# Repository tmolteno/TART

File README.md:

# Transient Array Radio Telescope

This repository has been ARCHIVED. It has been split into many smaller repositories under the tart-telescope organization.
see (https://github.com/tart-telescope) for details

The [Transient Array Radio Telescope](https://en.wikipedia.org/wiki/Transient_Array_Radio_Telescope) (TART) is a low-cost 24-element aperture synthesis array
developed by the [Elec Research Group](http://elec.ac.nz) at the University of Otago

 ![All-sky image from a TART telescope][tart_image] 

The TART software and hardware designs are released as open-source designs and are
licensed under the GPL v3.

The authors of the first version of the TART are Tim Molteno, Charles Shaw, Max 
Scheel and Phil Brown. Enquries about the TART should be addressed to Tim Molteno (tim@elec.ac.nz). 

[Connect to our development radio telescope here](https://tart.elec.ac.nz "Online Telescopes")

## Hardware

The TART hardware is designed using a combination of KiCAD (newest boards) and
CadSoft's Eagle package. These designs are located in the [hardware](hardware/README.md) folder. 

## Firmware

The TART uses an FPGA to synchronize data from each receiver. The code for this in the 
Verilog language is in the [hardware/FPGA](hardware/FPGA/README.md) directory

## Installation

See the  [Installation Instructions](INSTALL.md) file for more detail on installation.

[tart_image]: https://github.com/tmolteno/TART/blob/master/doc/img/tart_image.jpg "TART All-Sky Image"

## Telescope API documentation

The [Telescope API documentation](https://tart.elec.ac.nz/doc/) describes how the TART is controlled via the network for configration and data retrieval.

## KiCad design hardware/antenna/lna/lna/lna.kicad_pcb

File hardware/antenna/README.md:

# Antenna Design for TART

## Conventional GPS antenna

The TART telescope can operate with standard off-the-shelf antennas

 ![All-sky antenna on a pedestal (for snow clearance)][antenna_image] 

## Other Antenna Ideas

Goal. A simple radiation pattern insensitive to polarization with approximately 90 degree beam width.

[antenna_image]: https://github.com/tmolteno/TART/blob/master/doc/img/antenna.jpg "All-sky GPS antenna"

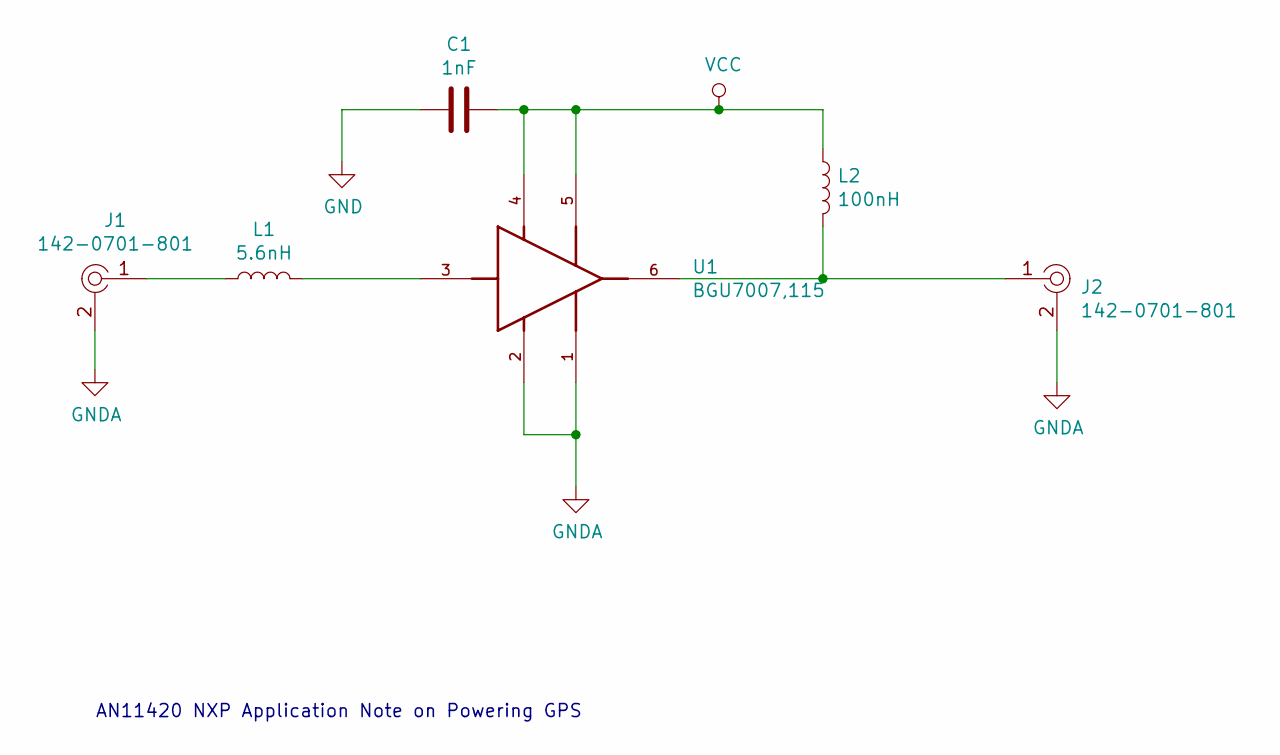
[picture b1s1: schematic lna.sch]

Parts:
C1: 1nF; C_0402_1005Metric
J1, J2: 142-0701-801; SMA_Amphenol_132289_EdgeMount; MPN 142-0701-801; Digi-Key_PN J502-ND
L1: 5.6nH; L_0402_1005Metric
L2: 100nH; L_0402_1005Metric
U1: BGU7007,115; PSON50P100X145X50-6N

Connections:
GND: C1.1
GNDA: J1.2, J2.2, U1.1 (GND1), U1.2 (GND2)
unnamed: J1.1, L1.1
unnamed: J2.1, L2.2, U1.6 (RF_OUT)
unnamed: L1.2, U1.3 (RF_IN)
VCC: C1.2, L2.1, U1.4 (VCC), U1.5 (ENABLE)

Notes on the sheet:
AN11420 NXP Application Note on Powering GPS

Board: 2 copper layers, 6 parts (0 on the bottom side), 5 nets, no tracks yet.

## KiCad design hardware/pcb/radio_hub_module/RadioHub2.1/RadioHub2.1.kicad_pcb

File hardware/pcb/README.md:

At the moment TART consists of three different PCBs:

1. (24x) Radio module (RF front end)
2. (4x) Radio hub module (jitter cleaner, power supply, 485 transceiver and base for 6 Radio modules)
3. (1x) Base station module (485 transceiver, oscillator, power supply, host for acquisition FPGA and Raspberry Pi)

base_station, radio_hub_module and radio_module are the original designs used for all currently built up TART's (as of Feb 2019). The base_station folder is a KIcad project, while radio_hub_module and radio_module are created in Eagle PCB.

The *201902 folder are the above converted and updated to KIcad 5 projects.

BOM html and CSV files are included. These are generated by the github.com:SchrodingersGat/KiBoM.git plugin.

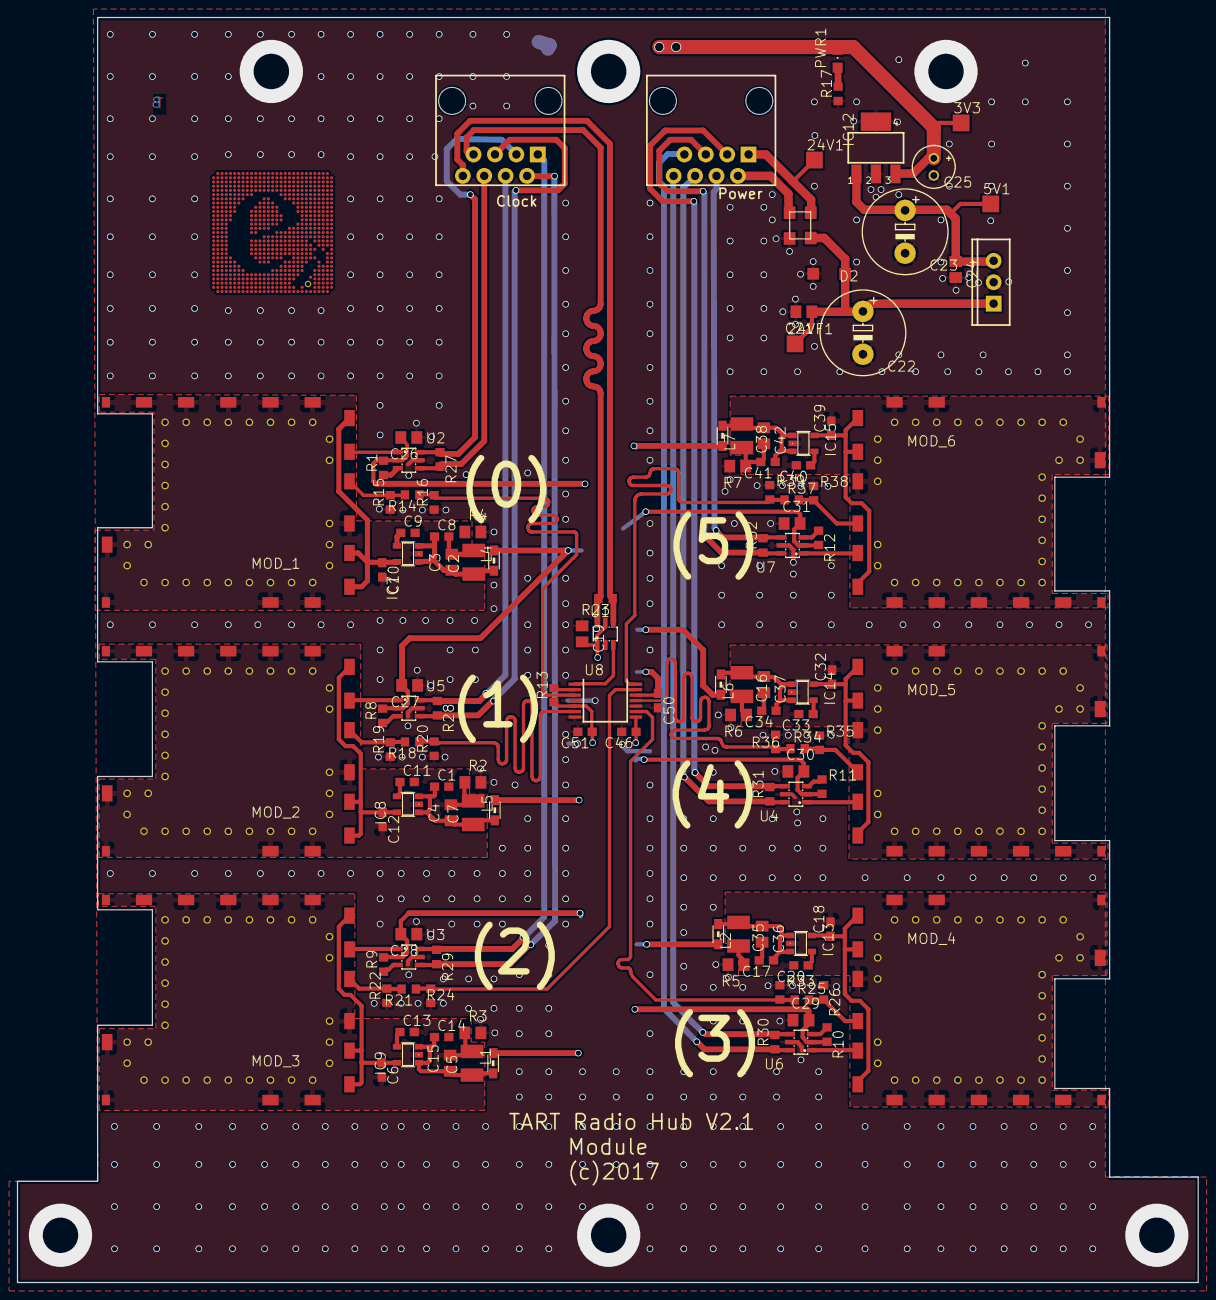
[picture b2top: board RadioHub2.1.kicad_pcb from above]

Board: 2 copper layers, 140.0 x 150.0 mm, 122 parts (0 on the bottom side), 71 nets.

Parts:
3V3, 5V1, 24V1, 24VF1: TPSQTP20SQ; TP20SQ
C1, C6, C8, C10, C12, C14, C17, C18, C32, C34, C39, C41: 1u; C0603
C2, C5, C7, C16, C35, C38: 220u; C1210
C3, C4, C15, C36, C37, C42: 0.1; C0805
C9, C11, C13, C20, C33, C40: 10n; C0603
C19, C21, C24, C26, C27, C28, C29, C30, C31: 0.1u; C0805
C22, C23: 100u; E5-10,5
C25: 10uF; E2-5
C46, C50, C51: 0.1; C0603
CON3, CON4: RJ45-8PTH; RJ45-8
D2: SMF24A; SOD123
IC7, IC8, IC9, IC13, IC14, IC15: TPS78227DDCR; SOT23-5
IC11: OKI78s05; TO220-IGO
IC12: SPX3940; SOT223
L1, L2, L4, L5, L6, L7: WE-CBF_0805; 0805
L3: ACM3225-601-2P-T001
MOD_1, MOD_2, MOD_3, MOD_4, MOD_5, MOD_6: GPS_RADIO_MODULE
PWR1: Red; CHIPLED_0805
R1, R8, R9, R10, R11, R12, R13, R17: 1k; R0603
R2, R3, R4, R5, R6, R7: 0 Ohm; R0805
R14, R18, R21, R25, R34, R37: 37.3; R0603
R15, R16, R19, R20, R22, R24, R26, R33, R35, R36, R38, R39: 151; R0603
R23, R27, R28, R29, R30, R31, R32: 100; R0603
U1: MAX3284E; SOT23-6L
U2, U3, U4, U5, U6, U7: MAX3295AUT; SOT23-6L
U8: CDCLVC1106; SSOP14
U$1: LOGO15X15; LOGO

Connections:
+3V3: 3V3.TP, C19.2, C25.+, C26.2, C27.2, C28.2, C29.2, C30.2, C31.2, C46.1, C50.1, C51.1, IC12.3, L1.1, L2.1, L4.1, L5.1, L6.1, L7.1, PWR1.C, R1.2, R8.2, R9.2, R10.2, R11.2, R12.2, R13.1, U1.1, U1.5, U2.2, U3.2, U4.2, U5.2, U6.2, U7.2, U8.5, U8.8, U8.12
+5V: 5V1.TP, C23.+, C24.1, IC11.OUT, IC12.1
/RadioHub2.1_2/+24V_CABLE: 24V1.TP, CON4.1, L3.1
/RadioHub2.1_2/CLK_N: CON3.7, R23.2, U1.6
/RadioHub2.1_2/CLK_P: CON3.8, R23.1, U1.4
/RadioHub2.1_2/GND_CABLE: CON4.2, L3.2
/RadioHub2.1_4/CLK0Y: R14.1, R16.2, U8.3
/RadioHub2.1_4/CLK1Y: R18.1, R20.2, U8.6
/RadioHub2.1_4/CLK2Y: R21.1, R24.2, U8.13
/RadioHub2.1_4/CLK3Y: R25.1, R33.2, U8.9
/RadioHub2.1_4/CLK4Y: R34.1, R36.2, U8.11
/RadioHub2.1_4/CLK5Y: R37.1, R39.2, U8.14
CLK0: MOD_1.CKIN@13, R14.2, R15.2
CLK1: MOD_2.CKIN@13, R18.2, R19.2
CLK2: MOD_3.CKIN@13, R21.2, R22.2
CLK3: MOD_4.CKIN@13, R25.2, R26.2
CLK4: MOD_5.CKIN@13, R34.2, R35.2
CLK5: MOD_6.CKIN@13, R37.2, R38.2
DT0_N: CON3.6, R27.2, U2.4
DT0_P: CON3.3, R27.1, U2.6
DT1_N: CON3.5, R28.2, U5.4
DT1_P: CON3.4, R28.1, U5.6
DT2_N: CON3.2, R29.2, U3.4
DT2_P: CON3.1, R29.1, U3.6
DT3_N: CON4.8, R30.2, U6.4
DT3_P: CON4.7, R30.1, U6.6
DT4_N: CON4.3, R31.2, U4.4
DT4_P: CON4.6, R31.1, U4.6
DT5_N: CON4.4, R32.2, U7.4
DT5_P: CON4.5, R32.1, U7.6
DT_0: MOD_1.DT@12, U2.1
DT_1: MOD_2.DT@12, U5.1
DT_2: MOD_3.DT@12, U3.1
DT_3: MOD_4.DT@12, U6.1
DT_4: MOD_5.DT@12, U4.1
DT_5: MOD_6.DT@12, U7.1
GND: C19.1, C21.2, C22.-, C23.-, C24.2, C25.-, C26.1, C27.1, C28.1, C29.1, C30.1, C31.1, C46.2, C50.2, C51.2, D2.A, IC11.GND, IC12.2, IC12.4, L3.3, R2.2, R3.2, R4.2, R5.2, R6.2, R7.2, R15.1, R16.1, R17.1, R19.1, R20.1, R22.1, R24.1, R26.1, R33.1, R35.1, R36.1, R38.1, R39.1, U1.2, U2.5, U3.5, U4.5, U5.5, U6.5, U7.5, U8.4, U8.7, U8.10
unnamed: 24VF1.TP, C21.1, C22.+, D2.C, IC11.IN, L3.4
unnamed: C1.1, C4.1, C7.1, IC8.1, IC8.3, L5.2
unnamed: C1.2, C4.2, C7.2, C11.2, C12.2, IC8.2, MOD_2.GND@1, MOD_2.GND@2, MOD_2.GND@3, MOD_2.GND@4, MOD_2.GND@5, MOD_2.GND@6, MOD_2.GND@7, MOD_2.GND@8, MOD_2.GND@9, MOD_2.GND@10, MOD_2.GND@14, MOD_2.V1, MOD_2.V2, MOD_2.V3, MOD_2.V4, MOD_2.V5, MOD_2.V6, MOD_2.V7, MOD_2.V8, MOD_2.V9, MOD_2.V10, MOD_2.V11, MOD_2.V12, MOD_2.V13, MOD_2.V14, MOD_2.V15, MOD_2.V16, MOD_2.V17, MOD_2.V18, MOD_2.V19, MOD_2.V20, MOD_2.V21, MOD_2.V22, MOD_2.V23, MOD_2.V24, MOD_2.V25, MOD_2.V26, MOD_2.V27, MOD_2.V28, MOD_2.V29, MOD_2.V30, R2.1
unnamed: C2.1, C3.1, C8.1, IC7.1, IC7.3, L4.2
unnamed: C6.1, IC9.5, MOD_3.2V8@11, MOD_3.2V8@15, MOD_3.2V8@16
unnamed: C9.1, IC7.4
unnamed: C10.1, IC7.5, MOD_1.2V8@11, MOD_1.2V8@15, MOD_1.2V8@16
unnamed: C2.2, C3.2, C8.2, C9.2, C10.2, IC7.2, MOD_1.GND@1, MOD_1.GND@2, MOD_1.GND@3, MOD_1.GND@4, MOD_1.GND@5, MOD_1.GND@6, MOD_1.GND@7, MOD_1.GND@8, MOD_1.GND@9, MOD_1.GND@10, MOD_1.GND@14, MOD_1.V1, MOD_1.V2, MOD_1.V3, MOD_1.V4, MOD_1.V5, MOD_1.V6, MOD_1.V7, MOD_1.V8, MOD_1.V9, MOD_1.V10, MOD_1.V11, MOD_1.V12, MOD_1.V13, MOD_1.V14, MOD_1.V15, MOD_1.V16, MOD_1.V17, MOD_1.V18, MOD_1.V19, MOD_1.V20, MOD_1.V21, MOD_1.V22, MOD_1.V23, MOD_1.V24, MOD_1.V25, MOD_1.V26, MOD_1.V27, MOD_1.V28, MOD_1.V29, MOD_1.V30, R4.1
unnamed: C11.1, IC8.4
unnamed: C12.1, IC8.5, MOD_2.2V8@11, MOD_2.2V8@15, MOD_2.2V8@16
unnamed: C13.1, IC9.4
unnamed: C5.2, C6.2, C13.2, C14.2, C15.2, IC9.2, MOD_3.GND@1, MOD_3.GND@2, MOD_3.GND@3, MOD_3.GND@4, MOD_3.GND@5, MOD_3.GND@6, MOD_3.GND@7, MOD_3.GND@8, MOD_3.GND@9, MOD_3.GND@10, MOD_3.GND@14, MOD_3.V1, MOD_3.V2, MOD_3.V3, MOD_3.V4, MOD_3.V5, MOD_3.V6, MOD_3.V7, MOD_3.V8, MOD_3.V9, MOD_3.V10, MOD_3.V11, MOD_3.V12, MOD_3.V13, MOD_3.V14, MOD_3.V15, MOD_3.V16, MOD_3.V17, MOD_3.V18, MOD_3.V19, MOD_3.V20, MOD_3.V21, MOD_3.V22, MOD_3.V23, MOD_3.V24, MOD_3.V25, MOD_3.V26, MOD_3.V27, MOD_3.V28, MOD_3.V29, MOD_3.V30, R3.1
unnamed: C5.1, C14.1, C15.1, IC9.1, IC9.3, L1.2
unnamed: C16.1, C34.1, C37.1, IC14.1, IC14.3, L6.2
unnamed: C16.2, C32.2, C33.2, C34.2, C37.2, IC14.2, MOD_5.GND@1, MOD_5.GND@2, MOD_5.GND@3, MOD_5.GND@4, MOD_5.GND@5, MOD_5.GND@6, MOD_5.GND@7, MOD_5.GND@8, MOD_5.GND@9, MOD_5.GND@10, MOD_5.GND@14, MOD_5.V1, MOD_5.V2, MOD_5.V3, MOD_5.V4, MOD_5.V5, MOD_5.V6, MOD_5.V7, MOD_5.V8, MOD_5.V9, MOD_5.V10, MOD_5.V11, MOD_5.V12, MOD_5.V13, MOD_5.V14, MOD_5.V15, MOD_5.V16, MOD_5.V17, MOD_5.V18, MOD_5.V19, MOD_5.V20, MOD_5.V21, MOD_5.V22, MOD_5.V23, MOD_5.V24, MOD_5.V25, MOD_5.V26, MOD_5.V27, MOD_5.V28, MOD_5.V29, MOD_5.V30, R6.1
unnamed: C17.1, C35.1, C36.1, IC13.1, IC13.3, L2.2
unnamed: C17.2, C18.2, C20.2, C35.2, C36.2, IC13.2, MOD_4.GND@1, MOD_4.GND@2, MOD_4.GND@3, MOD_4.GND@4, MOD_4.GND@5, MOD_4.GND@6, MOD_4.GND@7, MOD_4.GND@8, MOD_4.GND@9, MOD_4.GND@10, MOD_4.GND@14, MOD_4.V1, MOD_4.V2, MOD_4.V3, MOD_4.V4, MOD_4.V5, MOD_4.V6, MOD_4.V7, MOD_4.V8, MOD_4.V9, MOD_4.V10, MOD_4.V11, MOD_4.V12, MOD_4.V13, MOD_4.V14, MOD_4.V15, MOD_4.V16, MOD_4.V17, MOD_4.V18, MOD_4.V19, MOD_4.V20, MOD_4.V21, MOD_4.V22, MOD_4.V23, MOD_4.V24, MOD_4.V25, MOD_4.V26, MOD_4.V27, MOD_4.V28, MOD_4.V29, MOD_4.V30, R5.1
unnamed: C18.1, IC13.5, MOD_4.2V8@11, MOD_4.2V8@15, MOD_4.2V8@16
unnamed: C20.1, IC13.4
unnamed: C32.1, IC14.5, MOD_5.2V8@11, MOD_5.2V8@15, MOD_5.2V8@16
unnamed: C33.1, IC14.4
unnamed: C38.1, C41.1, C42.1, IC15.1, IC15.3, L7.2
unnamed: C38.2, C39.2, C40.2, C41.2, C42.2, IC15.2, MOD_6.GND@1, MOD_6.GND@2, MOD_6.GND@3, MOD_6.GND@4, MOD_6.GND@5, MOD_6.GND@6, MOD_6.GND@7, MOD_6.GND@8, MOD_6.GND@9, MOD_6.GND@10, MOD_6.GND@14, MOD_6.V1, MOD_6.V2, MOD_6.V3, MOD_6.V4, MOD_6.V5, MOD_6.V6, MOD_6.V7, MOD_6.V8, MOD_6.V9, MOD_6.V10, MOD_6.V11, MOD_6.V12, MOD_6.V13, MOD_6.V14, MOD_6.V15, MOD_6.V16, MOD_6.V17, MOD_6.V18, MOD_6.V19, MOD_6.V20, MOD_6.V21, MOD_6.V22, MOD_6.V23, MOD_6.V24, MOD_6.V25, MOD_6.V26, MOD_6.V27, MOD_6.V28, MOD_6.V29, MOD_6.V30, R7.1
unnamed: C39.1, IC15.5, MOD_6.2V8@11, MOD_6.2V8@15, MOD_6.2V8@16
unnamed: C40.1, IC15.4
unnamed: PWR1.A, R17.2
unnamed: R1.1, U2.3
unnamed: R8.1, U5.3
unnamed: R9.1, U3.3
unnamed: R10.1, U6.3
unnamed: R11.1, U4.3
unnamed: R12.1, U7.3
unnamed: R13.2, U8.2
RO_CLK: U1.3, U8.1

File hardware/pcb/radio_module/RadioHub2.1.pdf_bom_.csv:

Component,Description,Part,References,Value,Footprint,Quantity Per PCB,Datasheet,DIGIKEY,Notes
1,,TPSQTP20SQ,3V3 5V1 24V1 24VF1,TPSQTP20SQ,TP20SQ,4,,N/A,
2,,C-EUC0805,C3 C4 C15 C36 C37 C42,0.1,C0805,6,,,
3,,C-EUC0603,C46 C50 C51,0.1,C0603,3,,,
4,,C-EUC0805,C19 C21 C24 C26 C27 C28 C29 C30 C31,0.1u,C0805,9,,,
5,,CPOL-EUE5-10.5,C22 C23,100u,"E5-10,5",2,,,
6,,C-EUC0603,C9 C11 C13 C20 C33 C40,10n,C0603,6,,,
7,,CPOL-EUE2-5,C25,10uF,E2-5,1,,,
8,,C-EUC0603,C1 C6 C8 C10 C12 C14 C17 C18 C32 C34 C39 C41,1u,C0603,12,,,
9,,CPOL-EU1210,C2 C5 C7 C16 C35 C38,220u,C1210,6,,,
10,,RJ45-8PTH,CON3 CON4,RJ45-8PTH,RJ45-8,2,,609-1046-ND,Almost any 8p8c will do
11,,SMF24A,D2,UNI 24V TVS,SOD123,1,,F5823CT-ND,
12,,V_REG_OKI-78SRSINK,IC11,OKI78s05,TO220-IGO,1,,811-2196-5-ND,
13,,SPX3940,IC12,SPX3940,SOT223,1,,MCP1826S-3302E/DB-ND,
14,,NCP700BSN,IC7 IC8 IC9 IC13 IC14 IC15,TPS78227DDCR,SOT23-5,6,,296-23825-1-ND,
15,,ACM3225-601-2P-T001,L3,ACM3225-601-2P-T001,ACM3225-601-2P-T001,1,,,
16,,WE-CBF_0805,L1 L2 L4 L5 L6 L7,WE-CBF_0805,0805,6,,732-1620-1-ND,
17,,GPS_RADIO_MODULE,MOD_1 MOD_2 MOD_3 MOD_4 MOD_5 MOD_6,GPS_RADIO_MODULE,GPS_RADIO_MODULE,6,,N/A,
18,,LEDCHIPLED_0805,PWR1,Red,CHIPLED_0805,1,,,
19,,R-EU_R0805,R2 R3 R4 R5 R6 R7,0 Ohm,R0805,6,,,
20,,R-EU_R0603,R23 R27 R28 R29 R30 R31 R32,100,R0603,7,,,
21,,R-EU_R0603,R15 R16 R19 R20 R22 R24 R26 R33 R35 R36 R38 R39,151,R0603,12,,,
22,,R-EU_R0603,R1 R8 R9 R10 R11 R12 R13 R17,1k,R0603,8,,,
23,,R-EU_R0603,R14 R18 R21 R25 R34 R37,37.3,R0603,6,,,
24,,CDCLVC1106,U8,CDCLVC1106,SSOP14,1,,296-27588-1-ND,
25,,LOGO15X15,U$1,LOGO15X15,LOGO,1,,N/A,
26,,MAX3284E,U1,MAX3284E,SOT23-6L,1,,MAX3284EAUT+CT-ND,
27,,MAX3295AUT,U2 U3 U4 U5 U6 U7,MAX3295AUT,SOT23-6L,6,,ISL3295EIHZ-TCT-ND,





Component Groups:,27
Component Count:,122
Fitted Components:,122
Number of PCBs:,1
Total components:,122
Schematic Version:,
Schematic Date:,
BoM Date:,Thu 21 Feb 2019 17:07:20 NZDT
Schematic Source:,/home/phillb/TART/TART/hardware/pcb/hub201902/RadioHub2.1/RadioHub2.1.sch
KiCad Version:,Eeschema 5.0.2+dfsg1-1

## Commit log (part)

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2018-09-16 Added a little more context to the descri the description of the calibration
2018-09-20 Version bump and streamline dockerfiles
2018-09-20 Ignore node_modules in the docker files
2018-09-20 Use docker-compose to deploy the object position server
2018-09-28 Updated calibration docs.
2018-09-28 More doc cleanup, fix links
2018-09-28 Add a couple of containers for debug app builds - they reload when code is changed
2018-10-15 Added two QZS satellites to the correct list
2019-02-03 Some documentation cleanup
2019-02-06 Slight documentation improvements
2019-02-10 Improved install instructions with links.
2019-02-11 Added links to API documentation
2019-02-14 Add converted kicad projects
2019-02-14 Modify to upload antenna positions (take into account the rotation reported by the calibration)
2019-02-15 Updated the api handler to throw errors, and report SUCCESS when appropriate. Bump version and update dependencies. Closes #32 and Issue #38
2019-02-21 Move all the update and packages into a single command. This follows best practices and avoids stale apt caches
2019-02-21 Move to buster and python3
2019-02-21 Further python3 compatibility
2019-02-21 Added BOM stuff
2019-02-22 Change config attribute for num_antenna to get_num_antenna()
2019-02-22 Getting tests slowly working
2019-02-23 Updated API usage
2019-02-26 Import time, and catch exception correctly
2019-02-26 Moved things around so that old files are in the legacy directory
2019-02-27 Moved to directly using markdown from within setuptools
2019-03-03 Added a tunelling comment
2019-03-04 Some lint cleanup
2019-03-06 Finally working
2019-03-06 Now going
2019-03-06 Added argument parsing. Bringing up to date
2019-03-07 Added manifests
2019-03-08 Next step is visibility files
2019-03-09 Added HDF5 export and import for visibility objects
2019-03-10 Added dockerised testbench
2019-03-11 Update to add correct docker dependencies
2019-03-12 Clean up old compiled python files being used in the docker. HDF file saving now working
2019-03-12 Move to python3, handle HDF files
2019-03-12 Updated observation load to choose HDF files if the extension is right. Refers to Issue #40
2019-03-13 Update testbench to add visibility exporters for HDF format, and to rename Visibility_Load/Save to list_load and list_save, since they do not actually save individual visibility objects. Related to I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
2019-03-14 Better command line parsing, and check that the user specifies at least one option of data to download
2019-03-14 New raw data download function in tart tools
2019-03-14 Very slight typo in logging code
2019-05-08 Added a put method
2019-05-15 Update install instructions
2019-06-18 Updated README to reflect some pre-requisites. Relates to Issue #41
2019-07-02 Visibilities now stored as HDF5 files. Closes Issue #40
2019-07-08 Add some test dependencies
2019-07-24 Update to use new HDF data and python3 changes
2019-07-25 Added the raw image
2019-10-02 Added a timeout to HTTP requests
2019-11-05 Change table name to parameter
2019-11-06 Minor doc improvements
2019-11-06 Update to get locales right for casa
2019-11-06 Have added UVW data. fits file seems blank
2019-11-06 Have added many many tables
2019-11-07 Allow getting of information for the measurement set from the RESTful API
2020-02-20 Added docker-compose file for the VPN upstream connection
2020-03-15 Bump acorn from 5.1.2 to 5.7.4 in /software/containers/web_app/web-app
    Bumps [acorn](https://github.com/acornjs/acorn) from 5.1.2 to 5.7.4.
    - [Release notes](https://github.com/acornjs/acorn/releases)
    - [Commits](https://github.com/acornjs/acorn/compare/5.1.2...5.7.4)
2020-06-25 Bump rack in /software/containers/ephemeris_server/code
    Bumps [rack](https://github.com/rack/rack) from 1.6.11 to 2.1.4.
    - [Release notes](https://github.com/rack/rack/releases)
    - [Changelog](https://github.com/rack/rack/blob/master/CHANGELOG.md)
    - [Commits](https://github.com/rack/rack/compare/1.6.11...2.1.4)
2020-08-09 Add a header, and remove a special character in a comment
2020-08-25 Add gains and phases to stored hdf files
2020-09-14 Tag release 2.1. Closes #43
2021-03-08 Bump elliptic in /software/containers/web_app/web-app
    Bumps [elliptic](https://github.com/indutny/elliptic) from 6.5.0 to 6.5.4.
    - [Release notes](https://github.com/indutny/elliptic/releases)
    - [Commits](https://github.com/indutny/elliptic/compare/v6.5.0...v6.5.4)
2021-03-11 Fix jwt import
2021-04-12 Return a dict from the visibility.from_hdf5() method
2021-04-12 Minor documentation tweak
2021-04-14 Better baselines as lists
2021-05-07 Bump lodash in /software/containers/web_app/web-app
    Bumps [lodash](https://github.com/lodash/lodash) from 4.17.11 to 4.17.21.
    - [Release notes](https://github.com/lodash/lodash/releases)
    - [Commits](https://github.com/lodash/lodash/compare/4.17.11...4.17.21)
2021-05-19 Reformat code. Fix bug in get-gains handling in tart_calibrate
2021-05-19 Clean code using black
2021-05-27 Bump dns-packet in /software/containers/web_app/web-app
    Bumps [dns-packet](https://github.com/mafintosh/dns-packet) from 1.3.1 to 1.3.4.
    - [Release notes](https://github.com/mafintosh/dns-packet/releases)
    - [Changelog](https://github.com/mafintosh/dns-packet/blob/master/CHANGELOG.md)
    - [Commits](https://github.com/mafintosh/dns-packet/compare/v1.3.1...v1.3.4)
2021-06-11 Add resdme
2021-06-15 Removed hostname
2021-08-06 Reformat and port to python3
2021-10-05 Bump url-parse in /software/containers/web_app/web-app
    Bumps [url-parse](https://github.com/unshiftio/url-parse) from 1.4.7 to 1.5.3.
    - [Release notes](https://github.com/unshiftio/url-parse/releases)
    - [Commits](https://github.com/unshiftio/url-parse/compare/1.4.7...1.5.3)
    ---
    updated-dependencies:
    - dependency-name: url-parse
2021-11-04 Added template for gridless_wasm
2021-11-08 Cleaner code to do conditional assignment
2021-11-08 Added headers
2021-11-08 Library now returns a string
2021-11-11 example without bundler
2021-11-11 added wasm build dir for tart-vuer
2021-11-24 Added a README for build instructions
2021-12-04 Fix bug where spaces in satellite names causes a crash.
2021-12-14 Leave elevation and azimuth in degrees. Update max nside to 64
2022-01-09 Update docker-compose-telescope.yml
    Can directly run "docker-compose -f docker-compose-telescope.yml up --build"
2022-01-09 Update README.md
    Guide update
2022-01-21 Create fp-info-cache
2022-02-11 Bump karma from 4.1.0 to 6.3.14 in /software/containers/web_app/web-app
    Bumps [karma](https://github.com/karma-runner/karma) from 4.1.0 to 6.3.14.
    - [Release notes](https://github.com/karma-runner/karma/releases)
    - [Changelog](https://github.com/karma-runner/karma/blob/master/CHANGELOG.md)
    - [Commits](https://github.com/karma-runner/karma/compare/v4.1.0...v6.3.14)
    ---
    updated-dependencies:
2022-02-23 Compose for Rhodes
2022-02-26 Bump url-parse in /software/containers/web_app/web-app
    Bumps [url-parse](https://github.com/unshiftio/url-parse) from 1.4.7 to 1.5.10.
    - [Release notes](https://github.com/unshiftio/url-parse/releases)
    - [Commits](https://github.com/unshiftio/url-parse/compare/1.4.7...1.5.10)
    ---
    updated-dependencies:
    - dependency-name: url-parse
2022-04-01 Use k8 to run the script
2022-04-12 Bump nokogiri in /software/containers/ephemeris_server/code
    Bumps [nokogiri](https://github.com/sparklemotion/nokogiri) from 1.10.4 to 1.13.4.
    - [Release notes](https://github.com/sparklemotion/nokogiri/releases)
    - [Changelog](https://github.com/sparklemotion/nokogiri/blob/v1.13.4/CHANGELOG.md)
    - [Commits](https://github.com/sparklemotion/nokogiri/compare/v1.10.4...v1.13.4)
    ---
    updated-dependencies:
2022-05-02 support more flexible visibilities of baselines. selector for antennas in frontend. selector for tart api endpoint in frontend
2022-05-07 added deployment docs. fixed typo. staged build for rust->wasm and fronten.
2022-05-16 accept update
2022-06-01 Bump eventsource in /software/containers/web_app/web-app
    Bumps [eventsource](https://github.com/EventSource/eventsource) from 1.0.7 to 1.1.1.
    - [Release notes](https://github.com/EventSource/eventsource/releases)
    - [Changelog](https://github.com/EventSource/eventsource/blob/master/HISTORY.md)
    - [Commits](https://github.com/EventSource/eventsource/compare/v1.0.7...v1.1.1)
    ---
    updated-dependencies:
2022-06-20 Add ElAz test harness
2022-06-20 Update to modern development style. Add options to do a better fit
2022-06-20 Update scripts
2022-06-21 Added a --n parameter to stop after this many downloads
2022-06-21 Update with better help
2022-06-23 Update to use GHCR
2022-06-30 Remove duplicate classes that are in the tart codebase
2022-07-05 Remove objects that are now being used from tart.util
2022-07-05 Bump follow-redirects in /software/containers/web_app/web-app
    Bumps [follow-redirects](https://github.com/follow-redirects/follow-redirects) from 1.7.0 to 1.15.1.
    - [Release notes](https://github.com/follow-redirects/follow-redirects/releases)
    - [Commits](https://github.com/follow-redirects/follow-redirects/compare/v1.7.0...v1.15.1)
    ---
    updated-dependencies:
    - dependency-name: follow-redirects
2022-07-06 Moved to new repo
2022-07-23 Added north arm orientation and three arm survey
2022-07-25 Some data is here
2022-07-27 Added more measurements
2022-08-03 Add trigger ls command
2022-09-26 Bump degenerator and snyk in /software/containers/web_app/web-app
    Removes [degenerator](https://github.com/TooTallNate/node-degenerator). It's no longer used after updating ancestor dependency [snyk](https://github.com/snyk/snyk). These dependencies need to be upda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
    Removes `degenerator`
    Updates `snyk` from 1.134.2 to 1.1012.0
    - [Release notes](https://github.com/snyk/snyk/releases)
    - [Commits](https://github.com/snyk/snyk/compare/v1.134.2...v1.1012.0)
    ---
2022-10-21 Bump nokogiri in /software/containers/ephemeris_server/code
    Bumps [nokogiri](https://github.com/sparklemotion/nokogiri) from 1.13.6 to 1.13.9.
    - [Release notes](https://github.com/sparklemotion/nokogiri/releases)
    - [Changelog](https://github.com/sparklemotion/nokogiri/blob/main/CHANGELOG.md)
    - [Commits](https://github.com/sparklemotion/nokogiri/compare/v1.13.6...v1.13.9)
    ---
    updated-dependencies:
2022-11-15 Update Dockerfiles
2022-12-02 Bump decode-uri-component in /software/containers/web_app/web-app
    Bumps [decode-uri-component](https://github.com/SamVerschueren/decode-uri-component) from 0.2.0 to 0.2.2.
    - [Release notes](https://github.com/SamVerschueren/decode-uri-component/releases)
    - [Commits](https://github.com/SamVerschueren/decode-uri-component/compare/v0.2.0...v0.2.2)
    ---
    updated-dependencies:
    - dependency-name: decode-uri-component
2022-12-21 Add an elevation attribute for much smaller downloads
2023-02-01 Update rust packages
2023-10-13 Added five arm survey
2023-10-18 Update for Rhodes. Fix error in calculating bearing angle
2023-11-10 Added old antenna positions
2023-11-18 Use the new celestrak API
2025-03-27 Clean up code and update

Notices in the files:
hardware/pcb/radio_hub_module/RadioHub2.1/RadioHub2.1.kicad_pcb:
(c)2017
TART Radio Hub V2.1 Module (c)2017
